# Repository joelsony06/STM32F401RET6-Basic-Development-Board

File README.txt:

STM32F401RE Evaluation Board - Professional Clean Schematic

Open STM32F401RE_Eval.kicad_pro in KiCad. The schematic is legacy Eeschema format so KiCad may convert it to .kicad_sch on Save. The design intentionally includes explicit NC markers for unused MCU/USB pins, CC1/CC2 Rd resistors, proper reset/user circuits, and power flags for VBUS/GND/VCAP to reduce ERC errors.

Before fabrication: run ERC and DRC in your installed KiCad version and verify footprints/pin mapping against the STM32F401RE datasheet.

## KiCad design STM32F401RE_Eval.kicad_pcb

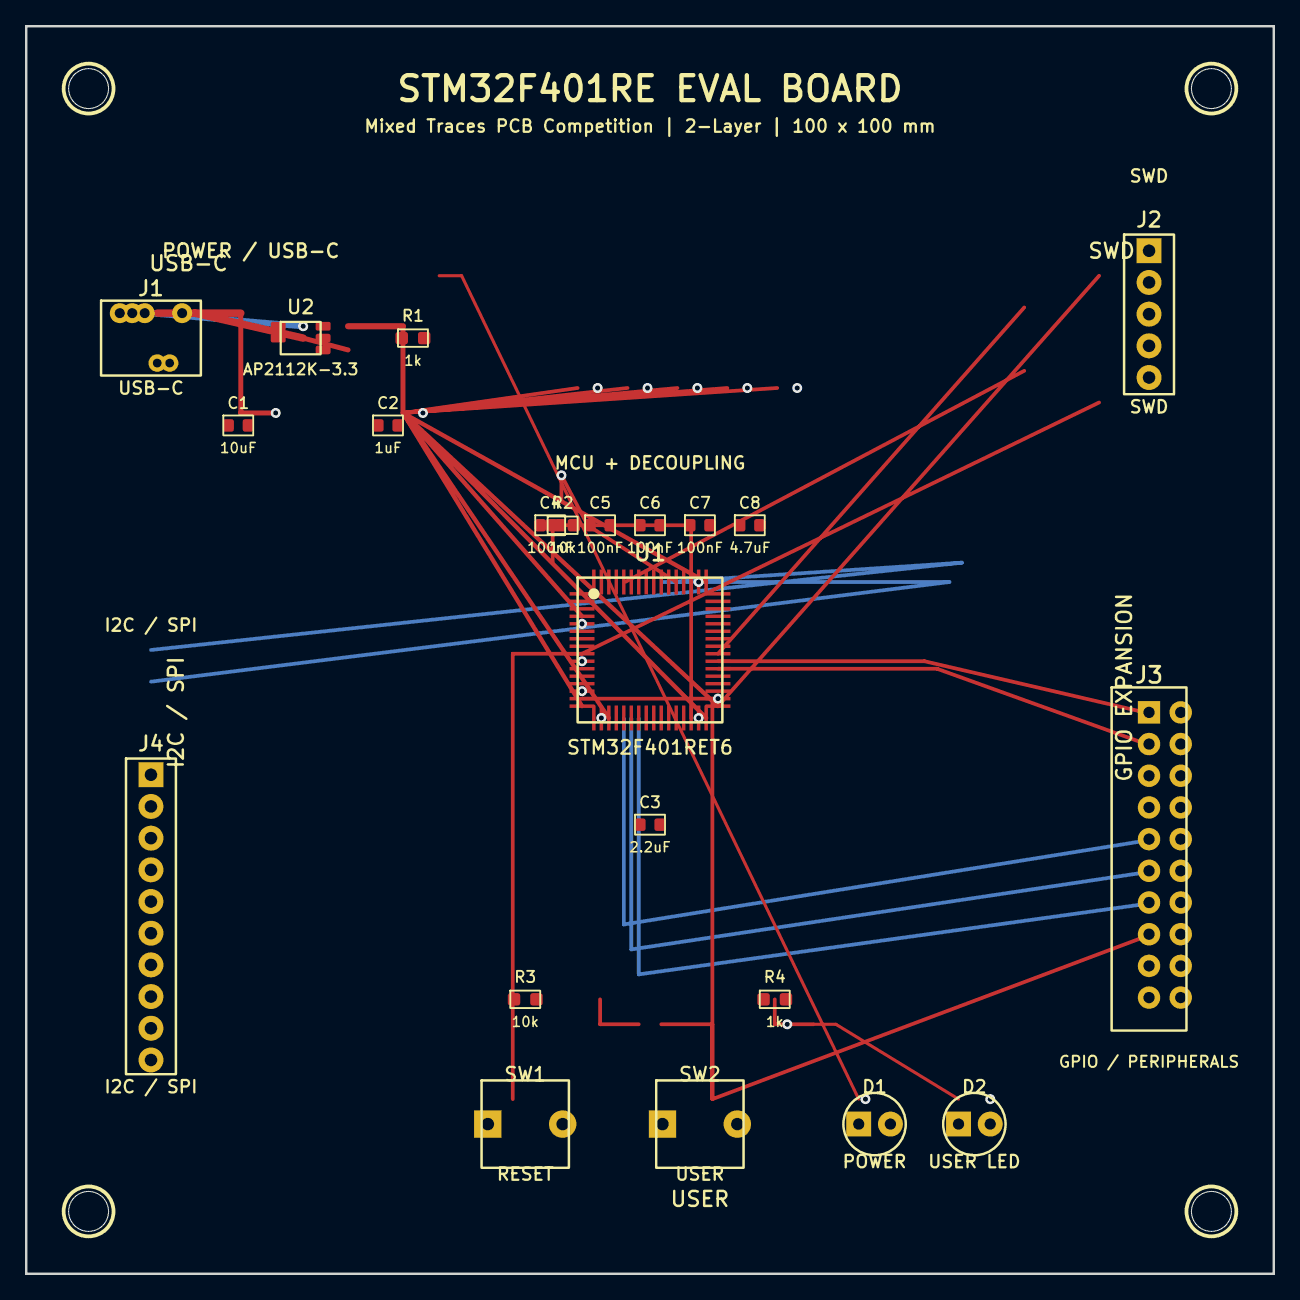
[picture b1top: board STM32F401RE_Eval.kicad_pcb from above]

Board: 2 copper layers, 100.0 x 100.0 mm, 26 parts (0 on the bottom side), 18 nets.

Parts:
C1: 10uF; C_0603
C2: 1uF; C_0603
C3: 2.2uF; C_0603
C4, C5, C6, C7: 100nF; C_0603
C8: 4.7uF; C_0603
D1: POWER; LED_D5.0mm
D2: USER LED; LED_D5.0mm
H1, H2, H3, H4: M3; MountingHole_3.2mm_M3
J1: USB-C; USB_C_Receptacle_GCT_USB4105-xx-A_16P_TopMnt_Horizontal
J2: SWD; PinHeader_1x05_P2.54mm_Vertical
J3: GPIO / PERIPHERALS; PinHeader_2x10_P2.54mm_Vertical
J4: I2C / SPI; PinHeader_1x10_P2.54mm_Vertical
R1, R4: 1k; R_0603
R2, R3: 10k; R_0603
SW1: RESET; SW_PUSH_6mm
SW2: USER; SW_PUSH_6mm
U1: STM32F401RET6; LQFP-64_10x10_P0.5
U2: AP2112K-3.3; SOT-23-5

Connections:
+3V3: C2.1, C4.1, C5.1, C6.1, C7.1, C8.1, J2.1, J3.1, J3.2, J4.7, R1.1, R3.1, R4.1, U1.1, U1.13, U1.19, U1.32, U1.48, U1.64, U2.3
BOOT0: R2.1, U1.60
GND: C1.2, C2.2, C3.2, C4.2, C5.2, C6.2, C7.2, C8.2, D1.2, D2.2, J1.A1, J1.A12, J2.3, J3.3, J3.4, J4.6, R2.2, SW1.2, SW2.2, U1.12, U1.18, U1.31, U1.47, U1.63, U2.1
I2C_SCL: J3.11, J3.12, J4.2, U1.58
I2C_SDA: J3.9, J3.10, J4.1, U1.59
LED_PWR: D1.1, R1.2
LED_USER: D2.1, R4.2
NRST: J2.5, SW1.1, U1.7
PC13: J3.19, J3.20, R3.2, SW2.1, U1.2
SPI_MISO: J3.15, J3.16, J4.4, U1.22
SPI_MOSI: J3.17, J3.18, J4.5, U1.23
SPI_SCK: J3.13, J3.14, J4.3, U1.21
SWCLK: J2.4, U1.49
SWDIO: J2.2, U1.46
UART_RX: J3.7, J3.8, U1.43
UART_TX: J3.5, J3.6, U1.42
VBUS_5V: C1.1, J1.A4, J1.A9, U2.2, U2.5
VCAP_1: C3.1, U1.30
